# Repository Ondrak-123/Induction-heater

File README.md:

Macondo link: https://macondo.hackclub.com/projects/6495
# Induction heater
- **This project is an Induction heater based on oscillation (ZVS-Zero Voltage Switching).**
- **The journal can be found at https://stasis.hackclub.com/dashboard/projects/cmmuu5lqf00kx01ns6pu1y2ej (project was started on Statis and now will be finished on Macondo!**
- **The journal features all guides, progress, explanations on how ZVS works and why it is the best way.**
  
**Why am I using softswitching and what is it?**

- Soft switch makes sure that the circuit is not powered instantly but after some time, when connecting an aligator clip or other power source you connect and disconnect the power supply multiple times which can fry the mosfets.

**Why is it called "Zero Voltage Switching"?**

- If one side of the circuit reaches zero volts, it triggers one MOSFET to turn on, while the other stays off and this cycle continues on and on.

**Why is it so efficient?**

- It is efficient thanks to the zero voltage switching, as you can probably tell by the name the mosfets switch at zero volts, thanks to this there is not as much heat generated.

_**Pictures:**_

Created a completely new BOM!:

| I will be using a seller based in the EU. (TME.EU). to avoid new tariff for the EU. I also included AliExpress link so everyone can do this project. I will have 2 orders one from JLCPCB that costs 8.44$. second one from TME.EU. all costs calculated in the total. |  |  |  |  |  |  |  |  |  |  |  |  |  |  |  |  |  |  |  |  |  |
| --- | --- | --- | --- | --- | --- | --- | --- | --- | --- | --- | --- | --- | --- | --- | --- | --- | --- | --- | --- | --- | --- |
| Name | Symbol/TME Code: | Purpose | Link: | Quantity needed: | Total Cost (CZK): | Total cost (USD): |  |  |  |  | Link | Distributor |  |  |  |  |  |  |  |  |  |
| PCB |  | From JLCPCB | * | 1 | *0* | $8.44 |  |  |  |  | https://jlcpcb.com/ | JLCPCB |  |  |  |  |  |  |  |  |  |
| IN4007 Diode |  | For soft starter. | * | 1 | *0* | *0* |  |  |  |  | https://www.aliexpress.com/item/1005010128860199.html?spm=a2g0o.productlist.main.13.321cVeUsVeUsDv&algo_pvid=5d1dc292-8c1d-47fc-b26f-221b35f9f573&algo_exp_id=5d1dc292-8c1d-47fc-b26f-221b35f9f573-31&pdp_ext_f=%7B%22order%22%3A%22320%22%2C%22eval%22%3A%221%22%2C%22fromPage%22%3A%22search%22%7D&pdp_npi=6%40dis%21USD%211.35%211.24%21%21%219.26%218.51%21%40211b61d017747780040114660e2416%2112000051243238520%21sea%21CZ%216063877758%21X%211%210%21n_tag%3A-29919%3Bd%3A1803c9ff%3Bm03_new_user%3A-29895%3BpisId%3A5000000203375670&curPageLogUid=wIl4TFkDRmTA&utparam-url=scene%3Asearch%7Cquery_from%3A%7Cx_object_id%3A1005010128860199%7C_p_origin_prod%3A | Aliexpress |  |  |  |  |  |  |  |  |  |
| Resistor 100KR |  | For soft starter. | * | 1 | *0* | *0* |  |  |  |  | https://www.aliexpress.com/item/1005007539842999.html?spm=a2g0o.productlist.main.13.77d7zj23zj23DF&algo_pvid=1429645b-4a36-4119-a7b3-98d736dedff9&algo_exp_id=1429645b-4a36-4119-a7b3-98d736dedff9-12&pdp_ext_f=%7B%22order%22%3A%2220994%22%2C%22eval%22%3A%221%22%2C%22orig_sl_item_id%22%3A%221005007539842999%22%2C%22orig_item_id%22%3A%221005006898731441%22%2C%22fromPage%22%3A%22search%22%7D&pdp_npi=6%40dis%21USD%213.01%211.50%21%21%2120.72%2110.36%21%402103849717747778049343615ed4db%2112000041212987998%21sea%21CZ%216063877758%21X%211%210%21n_tag%3A-29919%3Bd%3A1803c9ff%3Bm03_new_user%3A-29895&curPageLogUid=Yploor7BfNi6&utparam-url=scene%3Asearch%7Cquery_from%3A%7Cx_object_id%3A1005007539842999%7C_p_origin_prod%3A1005006898731441 | Aliexpress |  |  |  |  |  |  |  |  |  |
| Power cable |  | For power. HIGH AWG. | * | 1 | *0* | *0* |  |  |  |  | https://www.aliexpress.com/item/1005005203646529.html?spm=a2g0o.productlist.main.3.2506vKL4vKL4H0&algo_pvid=1ff6970a-e554-417a-9736-11d1abc39dd8&algo_exp_id=1ff6970a-e554-417a-9736-11d1abc39dd8-20&pdp_ext_f=%7B%22order%22%3A%223659%22%2C%22spu_best_type%22%3A%22price%22%2C%22eval%22%3A%221%22%2C%22fromPage%22%3A%22search%22%7D&pdp_npi=6%40dis%21USD%210.47%210.42%21%21%210.47%210.42%21%40211b813b17747164515903870eec0a%2112000032140706915%21sea%21CZ%210%21ABX%211%210%21n_tag%3A-29910%3Bd%3A1803c9ff%3Bm03_new_user%3A-29895&curPageLogUid=I0lyyNmGkllr&utparam-url=scene%3Asearch%7Cquery_from%3A%7Cx_object_id%3A1005005203646529%7C_p_origin_prod%3A | Aliexpress |  |  |  |  |  |  |  |  |  |
| Freewheeling diode SB1100 | SB1100-DIO | 100V 1A | https://www.tme.eu/cz/details/sb1100-dio/diody-schottky-tht/diotec-semiconductor/sb1100/ | 2 | 7.020 | *0* |  |  |  |  | https://www.aliexpress.com/item/1005007349885370.html?spm=a2g0o.productlist.main.1.6f9059c6bqkyBC&algo_pvid=39d6c1ab-6498-423b-9c55-4e7187bf4bcb&algo_exp_id=39d6c1ab-6498-423b-9c55-4e7187bf4bcb-0&pdp_ext_f=%7B%22order%22%3A%2266%22%2C%22spu_best_type%22%3A%22price%22%2C%22eval%22%3A%221%22%2C%22fromPage%22%3A%22search%22%7D&pdp_npi=6%40dis%21USD%212.32%210.99%21%21%2115.91%216.83%21%4021038da617740285924222759ed468%2112000040372339094%21sea%21CZ%210%21ABX%211%210%21n_tag%3A-29910%3Bd%3A1803c9ff%3Bm03_new_user%3A-29895%3BpisId%3A5000000197850273&curPageLogUid=PDHqQEwCMyGC&utparam-url=scene%3Asearch%7Cquery_from%3A%7Cx_object_id%3A1005007349885370%7C_p_origin_prod%3A | Aliexpress |  |  |  |  |  |  |  |  |  |
| Resistor 47R 5W | 5W-47R |  | https://www.tme.eu/cz/details/5w-47r/rezistory-tht/royalohm/mor05sj0470afi/ | 1 | 23.86 | *0* |  |  |  |  | https://www.aliexpress.com/item/1005007330288041.html?spm=a2g0o.productlist.main.46.767211fb70dwNG&aem_p4p_detail=202603201035359611494668413260001781554&algo_pvid=670cf7c4-ff83-4457-ae64-fbd872d743d6&algo_exp_id=670cf7c4-ff83-4457-ae64-fbd872d743d6-39&pdp_ext_f=%7B%22order%22%3A%22534%22%2C%22eval%22%3A%221%22%2C%22fromPage%22%3A%22search%22%7D&pdp_npi=6%40dis%21USD%210.66%210.54%21%21%214.49%213.68%21%4021038e1e17740281354252687e86c1%2112000040294719771%21sea%21CZ%210%21ABX%211%210%21n_tag%3A-29910%3Bd%3A1803c9ff%3Bm03_new_user%3A-29895&curPageLogUid=U4fOPbpAK6XU&utparam-url=scene%3Asearch%7Cquery_from%3A%7Cx_object_id%3A1005007330288041%7C_p_origin_prod%3A&search_p4p_id=202603201035359611494668413260001781554_10 | Aliexpress |  |  |  |  |  |  |  |  |  |
| Zener diode 15V 1W | 1N4744ATR |  | https://www.tme.eu/cz/details/1n4744atr/zenerovy-diody-tht/onsemi/ | 2 | 8.480 | *0* |  |  |  |  | https://www.aliexpress.com/item/1005006886308114.html?spm=a2g0o.productlist.main.12.763565e2VxvOFJ&algo_pvid=1daef451-8bd2-46a3-bdec-a26d66933992&algo_exp_id=1daef451-8bd2-46a3-bdec-a26d66933992-37&pdp_ext_f=%7B%22order%22%3A%2238%22%2C%22eval%22%3A%221%22%2C%22fromPage%22%3A%22search%22%7D&pdp_npi=6%40dis%21USD%211.83%210.99%21%21%211.83%210.99%21%402103956b17740280088897737e333c%2112000038620719183%21sea%21CZ%210%21ABX%211%210%21n_tag%3A-29910%3Bd%3A1803c9ff%3Bm03_new_user%3A-29895%3BpisId%3A5000000197850273&curPageLogUid=5Mdrg3XuXAoh&utparam-url=scene%3Asearch%7Cquery_from%3A%7Cx_object_id%3A1005006886308114%7C_p_origin_prod%3A | Aliexpress |  |  |  |  |  |  |  |  |  |
| Resistor 150R 5W | AC05-150R-5% |  | https://www.tme.eu/cz/details/ac05-150r-5%25/vykonne-rezistory/vishay/ac05000001500jac00/ | 2 | 43.86 | *0* |  |  |  |  | https://www.aliexpress.com/item/1005003645133625.html?spm=a2g0o.productlist.main.16.338e1d45dktWii&algo_pvid=601066ed-8d9a-4710-bbdd-b970ac96d48e&algo_exp_id=601066ed-8d9a-4710-bbdd-b970ac96d48e-8&pdp_ext_f=%7B%22order%22%3A%2256%22%2C%22eval%22%3A%221%22%2C%22fromPage%22%3A%22search%22%7D&pdp_npi=6%40dis%21USD%211.29%210.90%21%21%218.85%216.19%21%40211b80e117740277498711473ed231%2112000026631349304%21sea%21CZ%210%21ABX%211%210%21n_tag%3A-29910%3Bd%3A1803c9ff%3Bm03_new_user%3A-29895&curPageLogUid=fSkWTN76PRrU&utparam-url=scene%3Asearch%7Cquery_from%3A%7Cx_object_id%3A1005003645133625%7C_p_origin_prod%3A | Aliexpress |  |  |  |  |  |  |  |  |  |
| Thermal paste | QOLTEC-51630 | Better heat transfer. | https://www.tme.eu/cz/details/qoltec-51630/teplovodni-pasty/qoltec/51630/ | 2 | 45.02 | *0* |  |  |  |  | https://www.aliexpress.com/item/32833422141.html?spm=a2g0o.productlist.main.1.154ethvKthvKIr&algo_pvid=386a2713-dae7-4a0d-9e44-34a7fa4773e2&algo_exp_id=386a2713-dae7-4a0d-9e44-34a7fa4773e2-0&pdp_ext_f=%7B%22order%22%3A%22228%22%2C%22eval%22%3A%221%22%2C%22fromPage%22%3A%22search%22%7D&pdp_npi=6%40dis%21USD%210.79%210.52%21%21%210.79%210.52%21%40210391a017740270953226446ea508%2165038750325%21sea%21CZ%210%21ABX%211%210%21n_tag%3A-29910%3Bd%3A1803c9ff%3Bm03_new_user%3A-29895&curPageLogUid=HXpijeaxpZ5p&utparam-url=scene%3Asearch%7Cquery_from%3A%7Cx_object_id%3A32833422141%7C_p_origin_prod%3A | Aliexpress |  |  |  |  |  |  |  |  |  |
| Capacitor 220uF | CE-220/16PHT-Y | For soft starter. MOQ: 20 | https://www.tme.eu/cz/details/ce-220_16pht-y/elektrolyticke-kondenzatory-tht/aishi/ewh1cm221e11ot/ | 1 | 32.74 | *0* |  |  |  |  | https://www.aliexpress.com/item/1005007322240823.html?spm=a2g0o.productlist.main.3.4e4e6b597IeBnf&algo_pvid=02edfb23-74d5-47b3-b85f-622b369b29b5&algo_exp_id=02edfb23-74d5-47b3-b85f-622b369b29b5-2&pdp_ext_f=%7B%22order%22%3A%222020%22%2C%22spu_best_type%22%3A%22price%22%2C%22eval%22%3A%221%22%2C%22fromPage%22%3A%22search%22%7D&pdp_npi=6%40dis%21USD%211.23%210.86%21%21%211.23%210.86%21%40211b61bb17740248918105586ea653%2112000040256770954%21sea%21CZ%210%21ABX%211%210%21n_tag%3A-29910%3Bd%3A1803c9ff%3Bm03_new_user%3A-29895&curPageLogUid=mx3EbfFRgrpO&utparam-url=scene%3Asearch%7Cquery_from%3A%7Cx_object_id%3A1005007322240823%7C_p_origin_prod%3A | Aliexpress |  |  |  |  |  |  |  |  |  |
| Capacitor 1.5uF/2uF | C4AF9BU4150A1XK | ZVS switching. | https://www.tme.eu/cz/details/c4af9bu4150a1xk/kondenzatory-foliove-tht/kemet/ | 2 | 157.16 | *0* |  |  |  |  | https://www.tme.eu/cz/details/c4af9bu4150a1xk/kondenzatory-foliove-tht/kemet/ | Aliexpress |  |  |  |  |  |  |  |  |  |
| Resistor 10KR 5W | CRL5W-10K | ZVS switching. MOQ: 10 | https://www.tme.eu/cz/details/crl5w-10k/vykonne-rezistory/sr-passives/ | 2 | 28.46 | *0* |  |  |  |  | https://www.aliexpress.com/item/1005006363058219.html?spm=a2g0o.productlist.main.11.45e51d57BhhODY&algo_pvid=e61700af-3e94-40c6-837f-8b9eb99a6b25&algo_exp_id=e61700af-3e94-40c6-837f-8b9eb99a6b25-10&pdp_ext_f=%7B%22order%22%3A%22475%22%2C%22spu_best_type%22%3A%22price%22%2C%22eval%22%3A%221%22%2C%22fromPage%22%3A%22search%22%7D&pdp_npi=6%40dis%21USD%210.76%210.66%21%21%210.76%210.66%21%402103834817740246522776895e1674%2112000036899412422%21sea%21CZ%210%21ABX%211%210%21n_tag%3A-29910%3Bd%3A1803c9ff%3Bm03_new_user%3A-29895&curPageLogUid=xUFUBN3jZzu6&utparam-url=scene%3Asearch%7Cquery_from%3A%7Cx_object_id%3A1005006363058219%7C_p_origin_prod%3A | Aliexpress |  |  |  |  |  |  |  |  |  |
| Transistor 2N7000 | 2N7000-DIO | For soft starter. | https://www.tme.eu/cz/details/2n7000-dio/tranzistory-s-kanalem-n-tht/diotec-semiconductor/2n7000/ | 3 | 18.13 | *0* |  |  |  |  | https://www.aliexpress.com/item/1005007206189883.html?spm=a2g0o.productlist.main.10.52b815e34eyS3k&algo_pvid=1b9e943d-a183-49b7-ac1c-45ea658339a3&algo_exp_id=1b9e943d-a183-49b7-ac1c-45ea658339a3-48&pdp_ext_f=%7B%22order%22%3A%2225%22%2C%22spu_best_type%22%3A%22price%22%2C%22eval%22%3A%221%22%2C%22fromPage%22%3A%22search%22%7D&pdp_npi=6%40dis%21USD%210.94%210.94%21%21%210.94%210.94%21%40211b629217740244743261900e83ca%2112000039805368214%21sea%21CZ%210%21ABX%211%210%21n_tag%3A-29910%3Bd%3A1803c9ff%3Bm03_new_user%3A-29895&curPageLogUid=WkHDqQGZD8lz&utparam-url=scene%3Asearch%7Cquery_from%3A%7Cx_object_id%3A1005007206189883%7C_p_origin_prod%3A | Aliexpress |  |  |  |  |  |  |  |  |  |
| Inductors | DPT220A5 | Inductors 220uH. | https://www.tme.eu/cz/details/dpt220a5/tlumivky/ferrocore/ | 2 | 107.3 | *0* |  |  |  |  | https://www.aliexpress.com/item/1005009049853632.html?spm=a2g0o.productlist.main.31.774bojbOojbOFw&algo_pvid=b89a5244-83fa-4ea0-8365-d1b630e0f499&algo_exp_id=b89a5244-83fa-4ea0-8365-d1b630e0f499-30&pdp_ext_f=%7B%22order%22%3A%22147%22%2C%22eval%22%3A%221%22%2C%22fromPage%22%3A%22search%22%7D&pdp_npi=6%40dis%21USD%215.02%214.32%21%21%2134.38%2129.57%21%40210384b217740241582097454e3e8a%2112000047712666401%21sea%21CZ%210%21ABX%211%210%21n_tag%3A-29910%3Bd%3A1803c9ff%3Bm03_new_user%3A-29895&curPageLogUid=ZMnsTrP83ZAj&utparam-url=scene%3Asearch%7Cquery_from%3A%7Cx_object_id%3A1005009049853632%7C_p_origin_prod%3A | Aliexpress |  |  |  |  |  |  |  |  |  |
| Heatsink | SK104-38STS | Mosfet Cooling. | https://www.tme.eu/cz/details/sk104-38sts/chladice/fischer-elektronik/ | 2 | 129.23 | *0* |  |  |  |  | https://www.aliexpress.com/item/1005002711238683.html?spm=a2g0o.productlist.main.50.477a4914euPoik&algo_pvid=c910c5e1-95dc-480b-b3f9-444ed5662ba6&algo_exp_id=c910c5e1-95dc-480b-b3f9-444ed5662ba6-49&pdp_ext_f=%7B%22order%22%3A%22145%22%2C%22eval%22%3A%221%22%2C%22fromPage%22%3A%22search%22%7D&pdp_npi=6%40dis%21USD%213.88%211.88%21%21%213.88%211.88%21%40211b813b17739477792101402edb6e%2112000021815358235%21sea%21CZ%210%21ABXZ%211%210%21n_tag%3A-29910%3Bd%3A1803c9ff%3Bm03_new_user%3A-29895%3BpisId%3A5000000200562567&curPageLogUid=QgMZjcoePbgO&utparam-url=scene%3Asearch%7Cquery_from%3A%7Cx_object_id%3A1005002711238683%7C_p_origin_prod%3A | Aliexpress |  |  |  |  |  |  |  |  |  |
| Mosfet IRFB7730 | IRFB7730PBF | ZVS switching. | https://www.tme.eu/cz/details/irfb7730pbf/tranzistory-s-kanalem-n-tht/infineon-technologies/ | 2 | 159.04 | *0* |  |  |  |  | https://www.aliexpress.com/item/1005011844869795.html?spm=a2g0o.productlist.main.6.331aK3nTK3nTPQ&algo_pvid=cbc9dd74-dd5a-4a77-907d-66a1834d7ddf&algo_exp_id=cbc9dd74-dd5a-4a77-907d-66a1834d7ddf-5&pdp_ext_f=%7B%22order%22%3A%22-1%22%2C%22eval%22%3A%221%22%2C%22fromPage%22%3A%22search%22%7D&pdp_npi=6%40dis%21USD%214.54%214.54%21%21%2131.23%2131.23%21%40210388c917747806068723055e2327%2112000056762259380%21sea%21CZ%216063877758%21X%211%210%21n_tag%3A-29919%3Bd%3A1803c9ff%3Bm03_new_user%3A-29895&curPageLogUid=CfFBsAtcuWCR&utparam-url=scene%3Asearch%7Cquery_from%3A%7Cx_object_id%3A1005011844869795%7C_p_origin_prod%3A | Aliexpress |  |  |  |  |  |  |  |  |  |
| Coil |  | Few turns of solid copper wire. | * | 1 | *0* | *0* |  |  |  |  |  |  |  |  |  |  |  |  |  |  |  |
| TME Shipping |  |  | * |  | 169.41 | *0* |  |  |  |  |  |  |  |  |  |  |  |  |  |  |  |
|  |  |  |  |  | 929.71 CZK | 8.44USD |  |  |  | I will not be using these links. but I included them so you cam do this project even if you are not in EU. |  |  |  |  |  |  |  |  |  |  |  |
|  |  |  | 929.71CZK = | 44.97 USD |  |  |  |  |  |  |  |  |  |  |  |  |  |  |  |  |  |
|  |  |  |  | ´+8.44 USD |  |  |  |  |  |  |  |  |  |  |  |  |  |  |  |  |  |
|  |  |  | TOTAL: | 53.41 USD |  |  |  |  |  |  |  |  |  |  |  |  |  |  |  |  |  |
|  |  | REQUESTING AMOUNT: |  | 58 USD |  | SCREENSHOTS/CARTS BELOW!! |  |  |  |  |  |  |  |  |  |  |  |  |  |  |  |
|  |  |  |  |  |  | TME.EU |  |  |  |  |  |  |  |  |  |  |  |  |  |  | LCSC.COM |

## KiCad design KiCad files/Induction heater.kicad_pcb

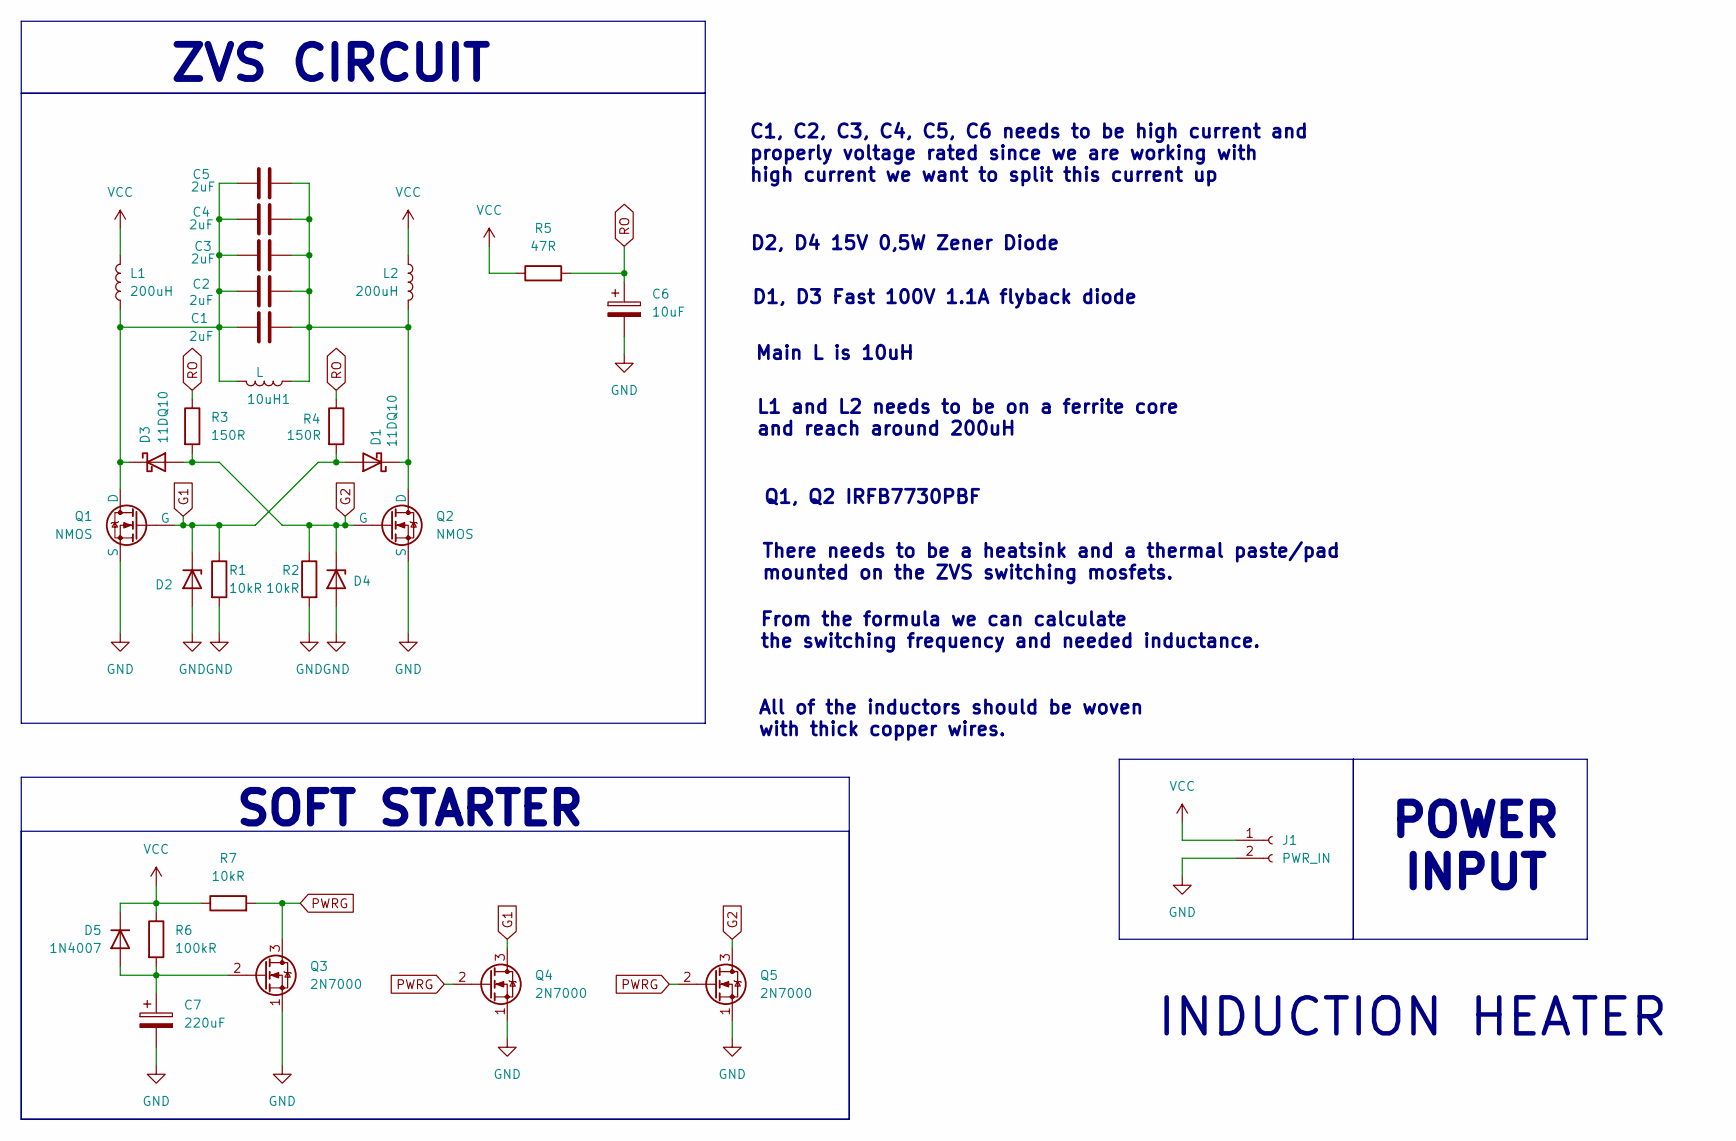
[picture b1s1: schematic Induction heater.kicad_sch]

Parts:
10uH1: L; PinHeader_1x02_P2.54mm_Vertical
C1, C2, C3, C4, C5: 2uF; C_Rect_L33.0mm_W20.0mm_P27.50mm_MKS4
C6: 10uF; CP_Radial_D8.0mm_P3.80mm
C7: 220uF; CP_Radial_D8.0mm_P3.80mm
D1, D3: 11DQ10; D_DO-41_SOD81_P12.70mm_Horizontal
D2: D_Zener; D_DO-41_SOD81_P12.70mm_Horizontal
D4: 15V, 0,5W; D_DO-41_SOD81_P12.70mm_Horizontal
D5: 1N4007; D_DO-41_SOD81_P10.16mm_Horizontal
J1: PWR_IN; SolderWire-6sqmm_1x02_P14mm_D3.5mm_OD7mm
L1, L2: 200uH; L_Toroid_Vertical_L21.6mm_W8.4mm_P8.38mm_Pulse_G
Q1, Q2: NMOS; TO-220-3_Vertical
Q3, Q4, Q5: 2N7000; TO-92_Inline
R1, R2, R7: 10kR; R_Axial_DIN0309_L9.0mm_D3.2mm_P12.70mm_Horizontal
R3, R4: 150R; R_Axial_DIN0309_L9.0mm_D3.2mm_P12.70mm_Horizontal
R5: 47R; R_Axial_DIN0309_L9.0mm_D3.2mm_P12.70mm_Horizontal
R6: 100kR; R_Axial_DIN0309_L9.0mm_D3.2mm_P12.70mm_Horizontal

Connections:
G1: D1.2 (A), D2.1 (K), Q1.2 (G), Q4.3 (D), R1.1, R4.2
G2: D3.2 (A), D4.1 (K), Q2.2 (G), Q5.3 (D), R2.1, R3.2
GND: C6.2, C7.2, D2.2 (A), D4.2 (A), J1.2, Q1.3 (S), Q2.3 (S), Q3.1 (S), Q4.1 (S), Q5.1 (S), R1.2, R2.2
unnamed 3: 10uH1.2, C1.2, C2.2, C3.2, C4.2, C5.2, D1.1 (K), L2.1, Q2.1 (D); also elsewhere on the board
unnamed 4: 10uH1.1, C1.1, C2.1, C3.1, C4.1, C5.1, D3.1 (K), L1.1, Q1.1 (D); also elsewhere on the board
unnamed: C7.1, D5.2 (A), Q3.2 (G), R6.2
PWRG: Q3.3 (D), Q4.2 (G), Q5.2 (G), R7.2
RO: C6.1, R3.1, R4.1, R5.2
VCC: D5.1 (K), J1.1, L1.2, L2.2, R5.1, R6.1, R7.1

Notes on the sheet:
C1, C2, C3, C4, C5, C6 needs to be high current and properly voltage rated since we are working with high current we want to split this current up
There needs to be a heatsink and a thermal paste/pad mounted on the ZVS switching mosfets.
ZVS CIRCUIT
L1 and L2 needs to be on a ferrite core and reach around 200uH
INDUCTION HEATER
D2, D4 15V 0,5W Zener Diode
Main L is 10uH
From the formula we can calculate the switching frequency and needed inductance.
SOFT STARTER
All of the inductors should be woven with thick copper wires.
POWER INPUT
D1, D3 Fast 100V 1.1A flyback diode
Q1, Q2 IRFB7730PBF

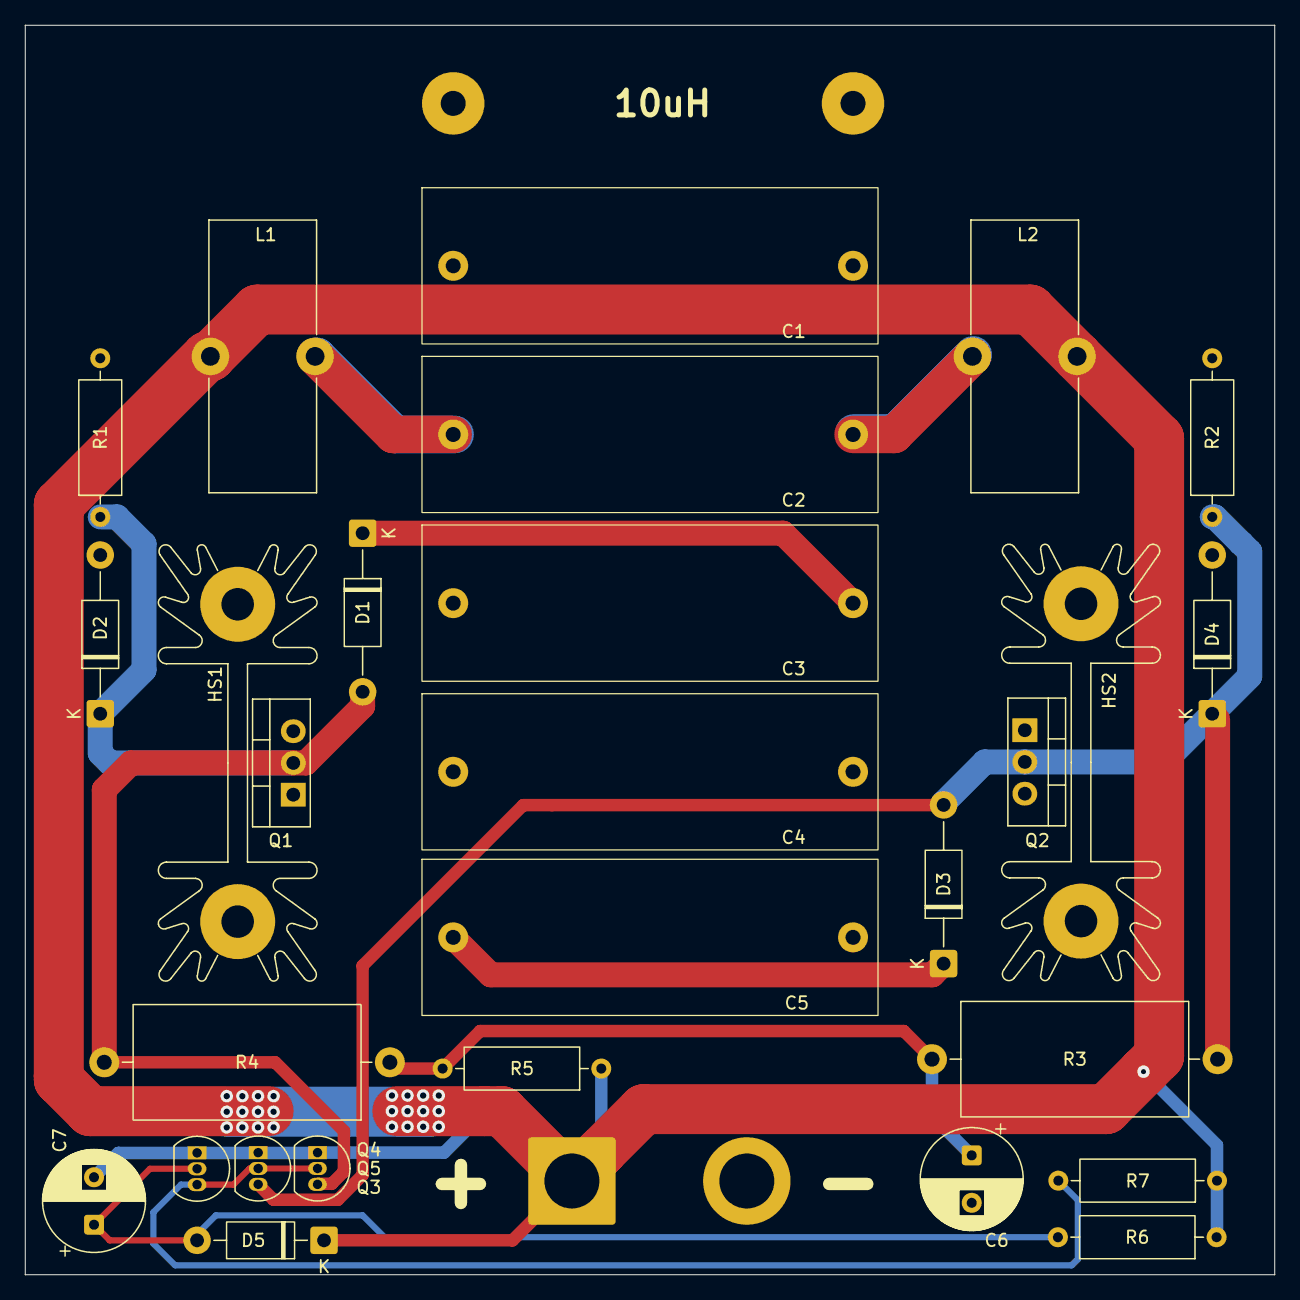
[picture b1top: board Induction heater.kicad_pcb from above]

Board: 2 copper layers, 100.0 x 100.0 mm, 30 parts (0 on the bottom side), 9 nets.

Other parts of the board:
10uH: L; PinHeader_1x02_P2.54mm_Vertical
HS1, HS2: Heatsink_AAVID_Extruded_531002B02100G_34.9x12.7mm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; Heatsink_AAVID_Extruded_531002B02100G_34.9x12.7mm_H25.4mm

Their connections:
unnamed 3: 10uH.1; also elsewhere on the board
unnamed 4: 10uH.1; also elsewhere on the board

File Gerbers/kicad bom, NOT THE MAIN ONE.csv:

Designator,Footprint,Quantity,Value,LCSC Part #
10UH,PinHeader_1x02_P2.54mm_Vertical,1,L,
"C1, C2, C3, C4, C5",C_Rect_L33.0mm_W20.0mm_P27.50mm_MKS4,5,2uF,
C6,CP_Radial_D8.0mm_P3.80mm,1,10uF,
C7,CP_Radial_D8.0mm_P3.80mm,1,220uF,
"D1, D3",D_DO-41_SOD81_P12.70mm_Horizontal,2,11DQ10,
D2,D_DO-41_SOD81_P12.70mm_Horizontal,1,D_Zener,
D4,D_DO-41_SOD81_P12.70mm_Horizontal,1,"15V, 0,5W",
D5,D_DO-41_SOD81_P10.16mm_Horizontal,1,1N4007,
"HS1, HS2",Heatsink_AAVID_Extruded_531002B02100G_34.9x12.7mm_H25.4mm,2,Heatsink_AAVID_Extruded_531002B02100G_34.9x12.7mm_H25.4mm,
J1,SolderWire-6sqmm_1x02_P14mm_D3.5mm_OD7mm,1,PWR_IN,
"L1, L2",L_Toroid_Vertical_L21.6mm_W8.4mm_P8.38mm_Pulse_G,2,200uH,
"Q1, Q2",TO-220-3_Vertical,2,NMOS,
"Q3, Q4, Q5",TO-92_Inline,3,2N7000,
"R1, R2, R7",R_Axial_DIN0309_L9.0mm_D3.2mm_P12.70mm_Horizontal,3,10kR,
"R3, R4",R_Axial_DIN0918_L18.0mm_D9.0mm_P22.86mm_Horizontal,2,150R,
R5,R_Axial_DIN0309_L9.0mm_D3.2mm_P12.70mm_Horizontal,1,47R,
R6,R_Axial_DIN0309_L9.0mm_D3.2mm_P12.70mm_Horizontal,1,100kR,

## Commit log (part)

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2026-03-29 Publish
2026-03-29 Added journal
    M, GitHub repository, and images of the project.
2026-03-29 BOM change
2026-05-11 README Update
2026-05-11 rename
2026-05-11 images updated
2026-06-07 delete
